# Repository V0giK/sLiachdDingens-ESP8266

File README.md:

# sLiachdDingens-ESP8266

**🛩️ Einfache 5-Kanal Modellflug Beleuchtungssteuerung**

Eine ESP8266-basierte Beleuchtungssteuerung für Modellflugzeuge mit webbasierter Konfiguration und flexiblen Lichtprofilen.

## ✨ Features

### Hardware
- **5 Ausgänge**: 3x 500mA, 2x 1A Belastbarkeit
- **Doppelte Anschlüsse**: Je Port 2 Steckplätze verfügbar
- **Universelle Stromversorgung**: 1-3S LiPo mit automatischer Erkennung
- **Kompaktes Design**: Optimiert für den Einbau in Modellflugzeuge

### Software
- **3 LightProfile**: Verschiedene Beleuchtungsmodi
- **Standalone-Betrieb**: Funktioniert auch ohne RC-Anlage
- **Web-Interface**: Konfiguration über WLAN-AccessPoint im Browser
- **RC-Integration**: 
  - Kanal 1: LightProfile-Umschaltung (3-Pos-Schalter)
  - Kanal 2: LowPower/MaxPower-Modus (2-Pos-Schalter oder Taster)
- **Intelligente Akkuüberwachung**: 
  - LowBatt-Warnung
  - Konfigurierbarer CutOff-Schutz
- **Flexible Blinksequenzen**: 
  - Vorgefertigte Sequenzen
  - Frei konfigurierbare Muster
- **OTA-Updates**: Firmware-Updates über WLAN
- **Backup-Funktion**: Download und Sicherung der Einstellungen

## 🔧 Installation

### Hardware-Aufbau

> ⚠️ **Wichtiger Hinweis**: Der ESP8266 sollte idealerweise **vor dem Einlöten** mit der OTA-fähigen Firmware geflasht werden! Als SMD-Bauteil ist das Flashen nach dem Verlöten über die seriellen Pins deutlich schwieriger zugänglich.

**Empfohlene Reihenfolge:**
1. **ESP8266 vorbereiten**: Filesystem und Firmware flashen (siehe Software-Installation)
2. **ESP8266 einlöten**: Bereits vorbereiteten ESP8266 SMD-Bauteil einbauen
3. **Weitere SMD-Bauteile löten**: ULA2003A und andere oberflächenmontierte Komponenten
4. **Anschlusskabel montieren**: Abschließende Verkabelung

**Hauptkomponenten:**
- ESP8266 Mikrocontroller (SMD)
- ULA2003A Treiber-IC (SMD)
- Weitere SMD-Komponenten (siehe Schaltplan)

### Software-Installation

> ⚠️ **Wichtig**: Reihenfolge beachten!

**Initial-Flash (vor dem Einlöten stark empfohlen):**
1. **Filesystem Upload** - Beinhaltet die wichtige `HW.json` mit EEPROM-Initialwerten
2. **Firmware Upload**
3. **Funktionstest** durchführen
4. **ESP8266 auf die Platine löten**

**Alternative (nach dem Einlöten):**
- OTA-Updates über das Web-Interface möglich
- Serielle Programmierung über die Programmierpins (bei SMD deutlich schwieriger)

## 🚀 Erste Schritte

1. ESP8266 mit Strom versorgen
2. WLAN-AccessPoint suchen (sLiachdDingens-XXXX)
3. Mit dem AccessPoint verbinden
4. Browser öffnen und zur Konfigurationsseite navigieren
5. Grundeinstellungen vornehmen:
   - Akkuspannungen konfigurieren
   - RC-Kanäle zuweisen
   - LightProfile anpassen

## 📋 Technische Daten

| Spezifikation | Wert |
|---------------|------|
| Eingangsspannung | 1-3S LiPo (3.7V - 12.6V) |
| Ausgänge | 5 Kanäle |
| Ausgangsleistung | 3x 500mA, 2x 1A |
| Mikrocontroller | ESP8266 (SMD) |
| Konfiguration | Web-Interface über WLAN |
| RC-Kanäle | 2 (optional) |

## 🔄 Entwicklungsstatus

> **🚧 In Entwicklung**
> 
> Dieses Projekt befindet sich aktiv in der Entwicklung. Features können sich ändern und neue Funktionen werden kontinuierlich hinzugefügt.

## 🤝 Beitragen

Feedback, Bug-Reports und Verbesserungsvorschläge sind willkommen! Erstellen Sie gerne ein Issue oder einen Pull Request.

## 📄 Lizenz

Dieses Projekt steht unter der [GNU GPL v3](LICENSE).  
Copyright © 2025 V0giK

Alle Abwandlungen und Forks dieses Projekts müssen ebenfalls unter den Bedingungen der GNU GPL v3 stehen.

---

**Made with ❤️ für die Modellflug-Community**

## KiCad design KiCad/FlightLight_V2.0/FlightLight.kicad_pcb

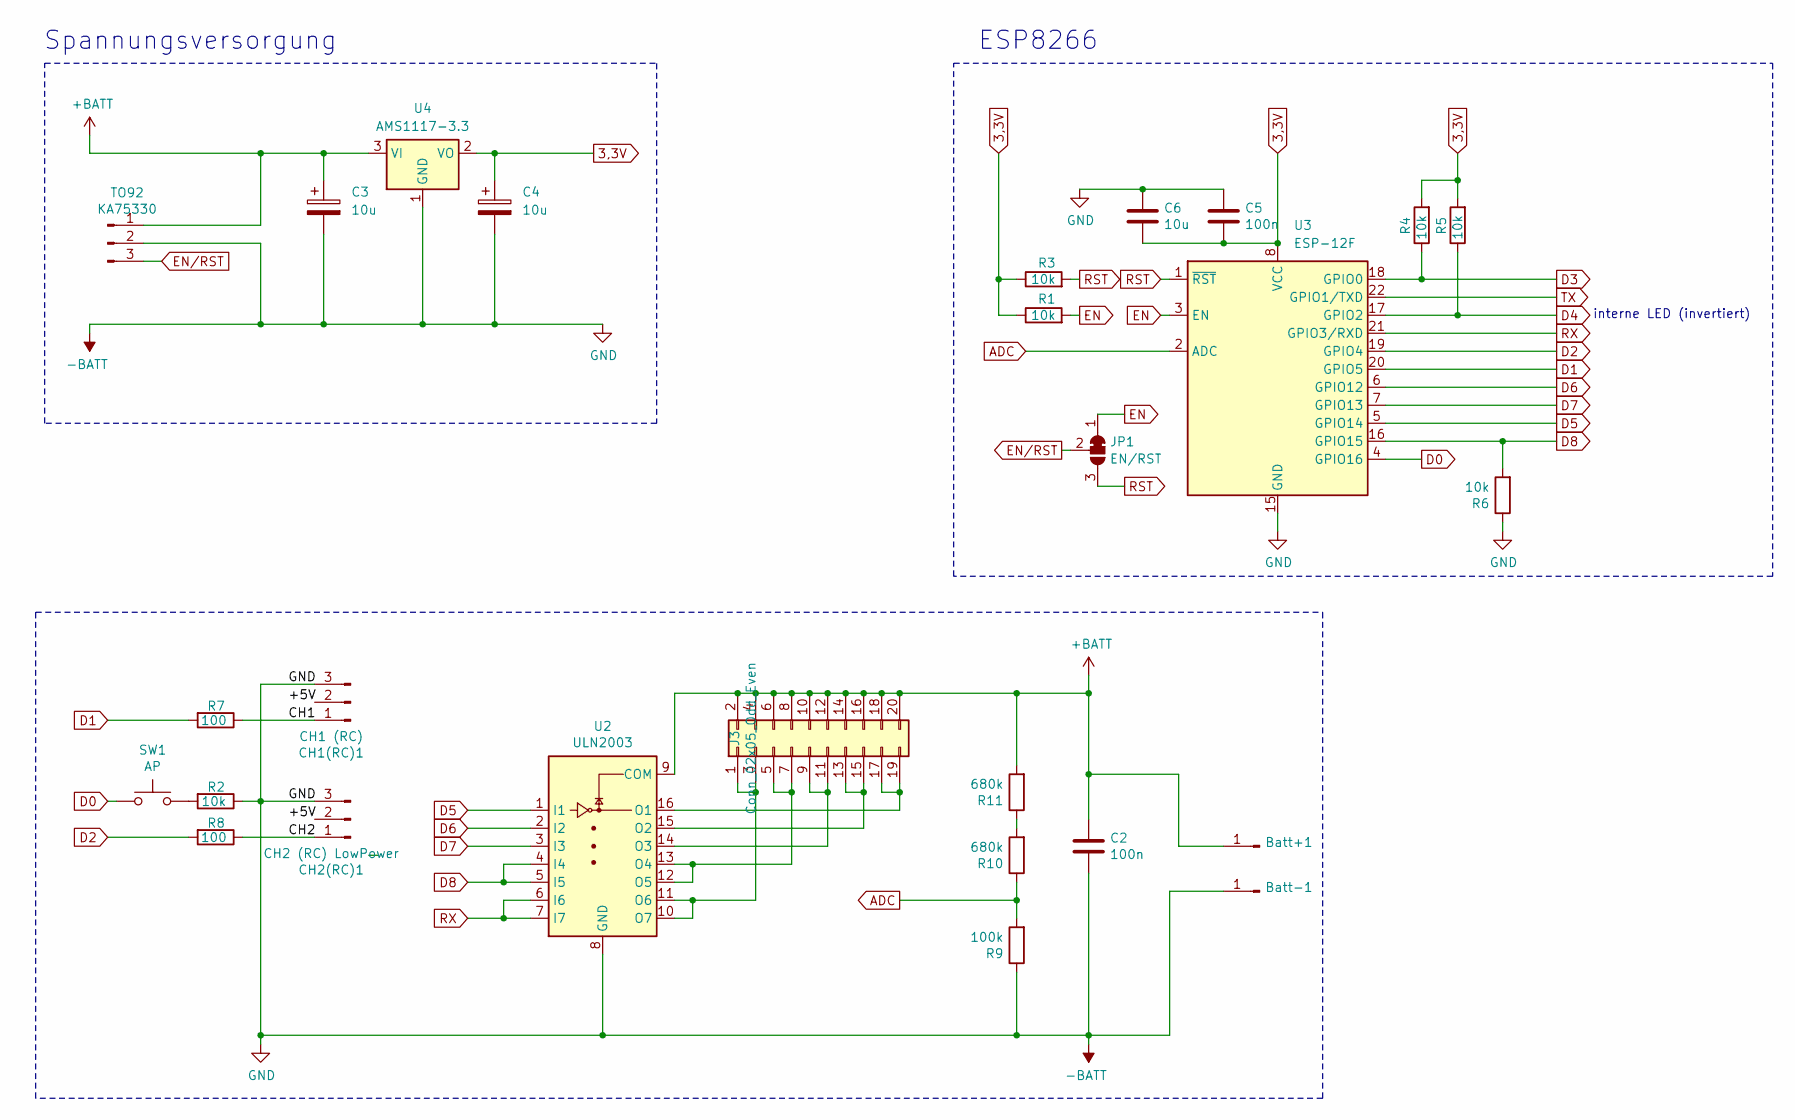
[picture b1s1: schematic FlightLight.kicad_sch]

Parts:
Batt+1: Batt+; Conn_01x01_2.54
Batt-1: Batt-; Conn_01x01_2.54
C2, C5: 100n; C_0805_2012Metric_Pad1.18x1.45mm_HandSolder
C3, C4, C6: 10u; C_0805_2012Metric_Pad1.18x1.45mm_HandSolder
CH1(RC)1: CH1 (RC); Conn_01x03_2.54_small
CH2(RC)1: CH2 (RC) LowPower; Conn_01x03_2.54_small
J3: Conn_02x05_Odd_Even; PinHeader_2x10_P2.54mm_Vertical
JP1: EN/RST; SolderJumper-3_P1.3mm_Bridged12_RoundedPad1.0x1.5mm
R1, R2, R3, R4, R5, R6: 10k; R_0805_2012Metric_Pad1.20x1.40mm_HandSolder
R7, R8: 100; R_0805_2012Metric_Pad1.20x1.40mm_HandSolder
R9: 100k; R_0805_2012Metric_Pad1.20x1.40mm_HandSolder
R10, R11: 680k; R_0805_2012Metric_Pad1.20x1.40mm_HandSolder
SW1: AP; SW_Push_1P1T_NO_4.5x4.5mm_H7mm
TO92: KA75330; Conn_01x03_2.54_small
U2: ULN2003; SO-16_3.9x9.9mm_P1.27mm
U3: ESP-12F; ESP-12S
U4: AMS1117-3.3; SOT-223-3_TabPin2

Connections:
3,3V: C4.1, C5.2, C6.2, R1.1, R3.1, R4.2, R5.2, U3.8 (VCC), U4.2 (VO)
+BATT: Batt+1.1, C2.1, C3.1, J3.2, J3.4, J3.6, J3.8, J3.10, J3.12, J3.14, J3.16, J3.18, J3.20, R11.2, TO92.1, U2.9 (COM), U4.3 (VI)
-BATT: Batt-1.1, C2.2, C3.2, C4.2, C5.1, C6.1, CH1(RC)1.3, CH2(RC)1.3, R2.1, R6.1, R9.1, TO92.2, U2.8 (GND), U3.15 (GND), U4.1 (GND)
/CH1: CH1(RC)1.1, R7.1
/CH2: CH2(RC)1.1, R8.1
ADC: R9.2, R10.1, U3.2 (ADC)
D0: SW1.1, U3.4 (GPIO16)
D1: R7.2, U3.20 (GPIO5)
D2: R8.2, U3.19 (GPIO4)
D3: R4.1, U3.18 (GPIO0)
D4: R5.1, U3.17 (GPIO2)
D5: U2.1 (I1), U3.5 (GPIO14)
D6: U2.2 (I2), U3.6 (GPIO12)
D7: U2.3 (I3), U3.7 (GPIO13)
D8: R6.2, U2.4 (I4), U2.5 (I5), U3.16 (GPIO15)
EN: JP1.1 (A), R1.2, U3.3 (EN)
EN/RST: JP1.2 (C), TO92.3
unnamed: J3.1, J3.3, U2.10 (O7), U2.11 (O6)
unnamed: J3.5, J3.7, U2.12 (O5), U2.13 (O4)
unnamed: J3.9, J3.11, U2.14 (O3)
unnamed: J3.13, J3.15, U2.15 (O2)
unnamed: J3.17, J3.19, U2.16 (O1)
unnamed: R2.2, SW1.2
unnamed: R10.2, R11.1
RST: JP1.3 (B), R3.2, U3.1 (~RST)
RX: U2.6 (I6), U2.7 (I7), U3.21 (GPIO3/RXD)
TX: U3.22 (GPIO1/TXD)

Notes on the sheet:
ESP8266
Spannungsversorgung
interne LED (invertiert)

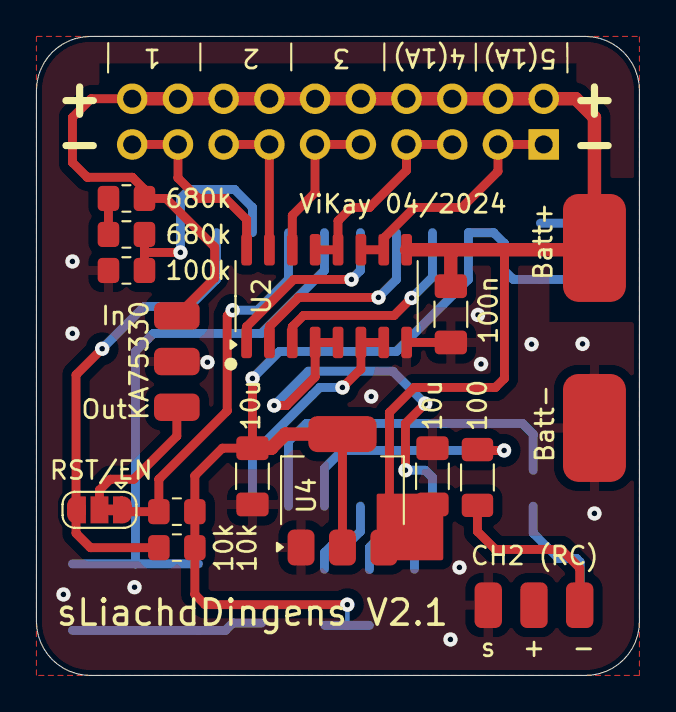
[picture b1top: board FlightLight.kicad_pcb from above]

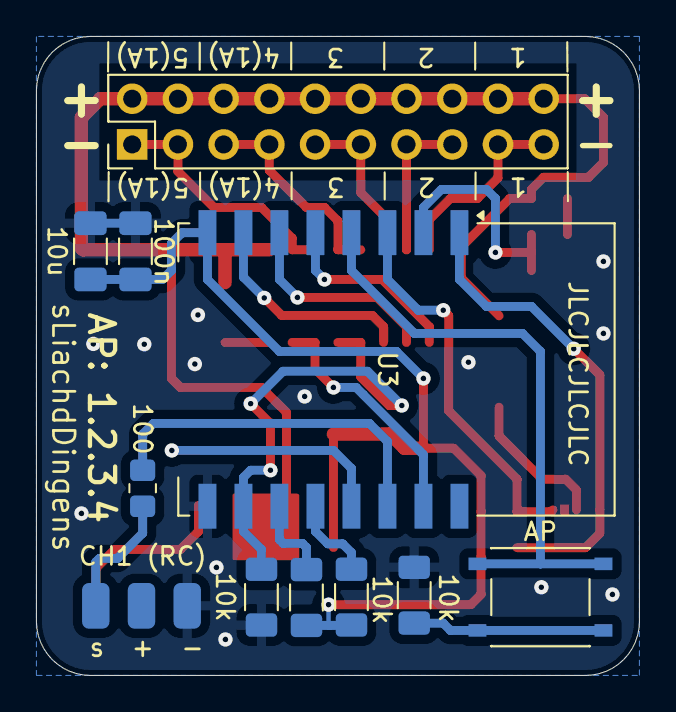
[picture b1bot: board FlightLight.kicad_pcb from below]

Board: 2 copper layers, 33.5 x 35.5 mm, 27 parts (11 on the bottom side), 26 nets.

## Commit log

2024-04-01 Add files via upload
    Initial upload
2024-04-02 Entwicklungsstand
2024-04-02 panelize ausgerichtet
2024-04-02 init
2024-04-03 new panelized
2024-04-12 new file: PlatformIO/Default OTA/.gitignore new file: PlatformIO/Default OTA/.vscode/extensions.json new file: PlatformIO/Default OTA/include/README new file: PlatformIO/Default OTA/lib/README new fi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
2024-04-12 arange files
2024-04-15 Board Fix
2024-04-15 first runnable version
2024-04-15 Nach WLAN Login LED an.
2024-04-15 Fix V2.1 - Pin TX nicht verwenden
2024-04-15 Fix EEPROM read bei HW.json
2024-04-21 PCB V2.1
    kleine Fixes
2025-05-12 Update issue templates
2025-05-12 Create LICENSE
2025-05-12 Update LICENSE
2025-08-18 optmize
2025-08-18 README
2025-08-18 Updated README file with improved content
2025-08-18 cleanup
2025-09-02 fix: ElegantOTA new version
